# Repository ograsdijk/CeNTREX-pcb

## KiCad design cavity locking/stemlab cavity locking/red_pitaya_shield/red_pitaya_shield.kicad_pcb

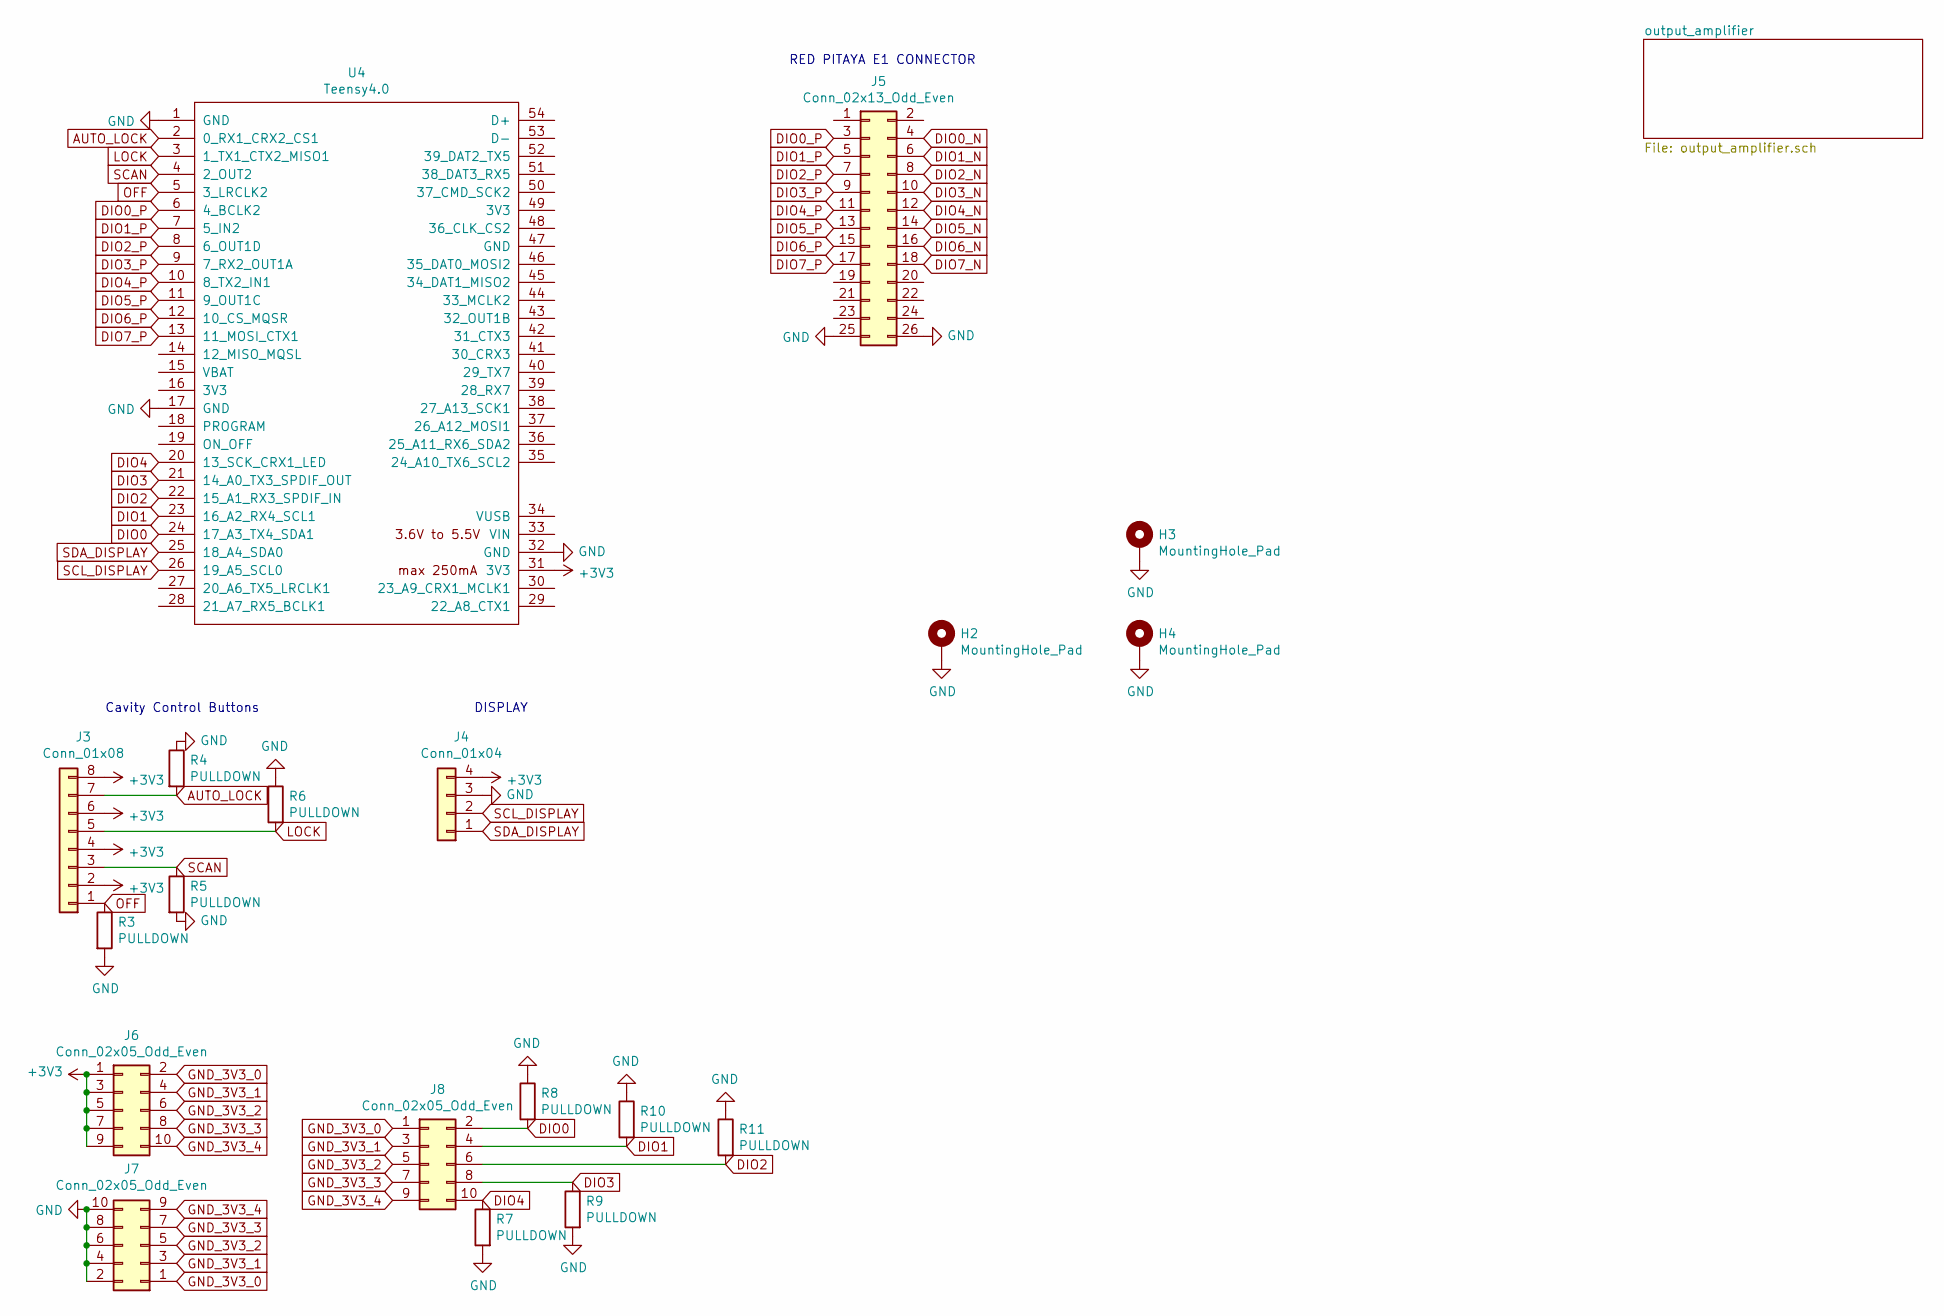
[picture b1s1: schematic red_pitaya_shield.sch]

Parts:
H2, H3, H4: MountingHole_Pad; MountingHole_3.2mm_M3_DIN965_Pad
J3: Conn_01x08; PinHeader_2x04_P2.54mm_Vertical
J4: Conn_01x04; PinHeader_1x04_P2.54mm_Vertical
J5: Conn_02x13_Odd_Even; IDC-Header_2x13_P2.54mm_Vertical
J6, J7, J8: Conn_02x05_Odd_Even; PinSocket_2x05_P2.54mm_Vertical
R3, R4, R5, R6, R7, R8, R9, R10, R11: PULLDOWN; R_0805_2012Metric
U4: Teensy4.0; Teensy40

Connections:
+3V3: J3.2, J3.4, J3.6, J3.8, J4.4, J6.1, J6.3, J6.5, J6.7, J6.9, U4.31 (3V3)
AUTO_LOCK: J3.7, R4.2, U4.2 (0_RX1_CRX2_CS1)
DIO0: J8.2, R8.2, U4.24 (17_A3_TX4_SDA1)
DIO0_N: J5.4
DIO0_P: J5.3, U4.6 (4_BCLK2)
DIO1: J8.4, R10.2, U4.23 (16_A2_RX4_SCL1)
DIO1_N: J5.6
DIO1_P: J5.5, U4.7 (5_IN2)
DIO2: J8.6, R11.2, U4.22 (15_A1_RX3_SPDIF_IN)
DIO2_N: J5.8
DIO2_P: J5.7, U4.8 (6_OUT1D)
DIO3: J8.8, R9.1, U4.21 (14_A0_TX3_SPDIF_OUT)
DIO3_N: J5.10
DIO3_P: J5.9, U4.9 (7_RX2_OUT1A)
DIO4: J8.10, R7.1, U4.20 (13_SCK_CRX1_LED)
DIO4_N: J5.12
DIO4_P: J5.11, U4.10 (8_TX2_IN1)
DIO5_N: J5.14
DIO5_P: J5.13, U4.11 (9_OUT1C)
DIO6_N: J5.16
DIO6_P: J5.15, U4.12 (10_CS_MQSR)
DIO7_N: J5.18
DIO7_P: J5.17, U4.13 (11_MOSI_CTX1)
GND: H2.1, H3.1, H4.1, J4.3, J5.25, J5.26, J7.2, J7.4, J7.6, J7.8, J7.10, R3.2, R4.1, R5.2, R6.1, R7.2, R8.1, R9.2, R10.1, R11.1, U4.1 (GND), U4.17 (GND), U4.32 (GND); also elsewhere on the board
GND_3V3_0: J6.2, J7.1, J8.1
GND_3V3_1: J6.4, J7.3, J8.3
GND_3V3_2: J6.6, J7.5, J8.5
GND_3V3_3: J6.8, J7.7, J8.7
GND_3V3_4: J6.10, J7.9, J8.9
LOCK: J3.5, R6.2, U4.3 (1_TX1_CTX2_MISO1)
OFF: J3.1, R3.1, U4.5 (3_LRCLK2)
SCAN: J3.3, R5.1, U4.4 (2_OUT2)
SCL_DISPLAY: J4.2, U4.26 (19_A5_SCL0)
SDA_DISPLAY: J4.1, U4.25 (18_A4_SDA0)

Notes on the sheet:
Cavity Control Buttons
RED PITAYA E1 CONNECTOR
DISPLAY

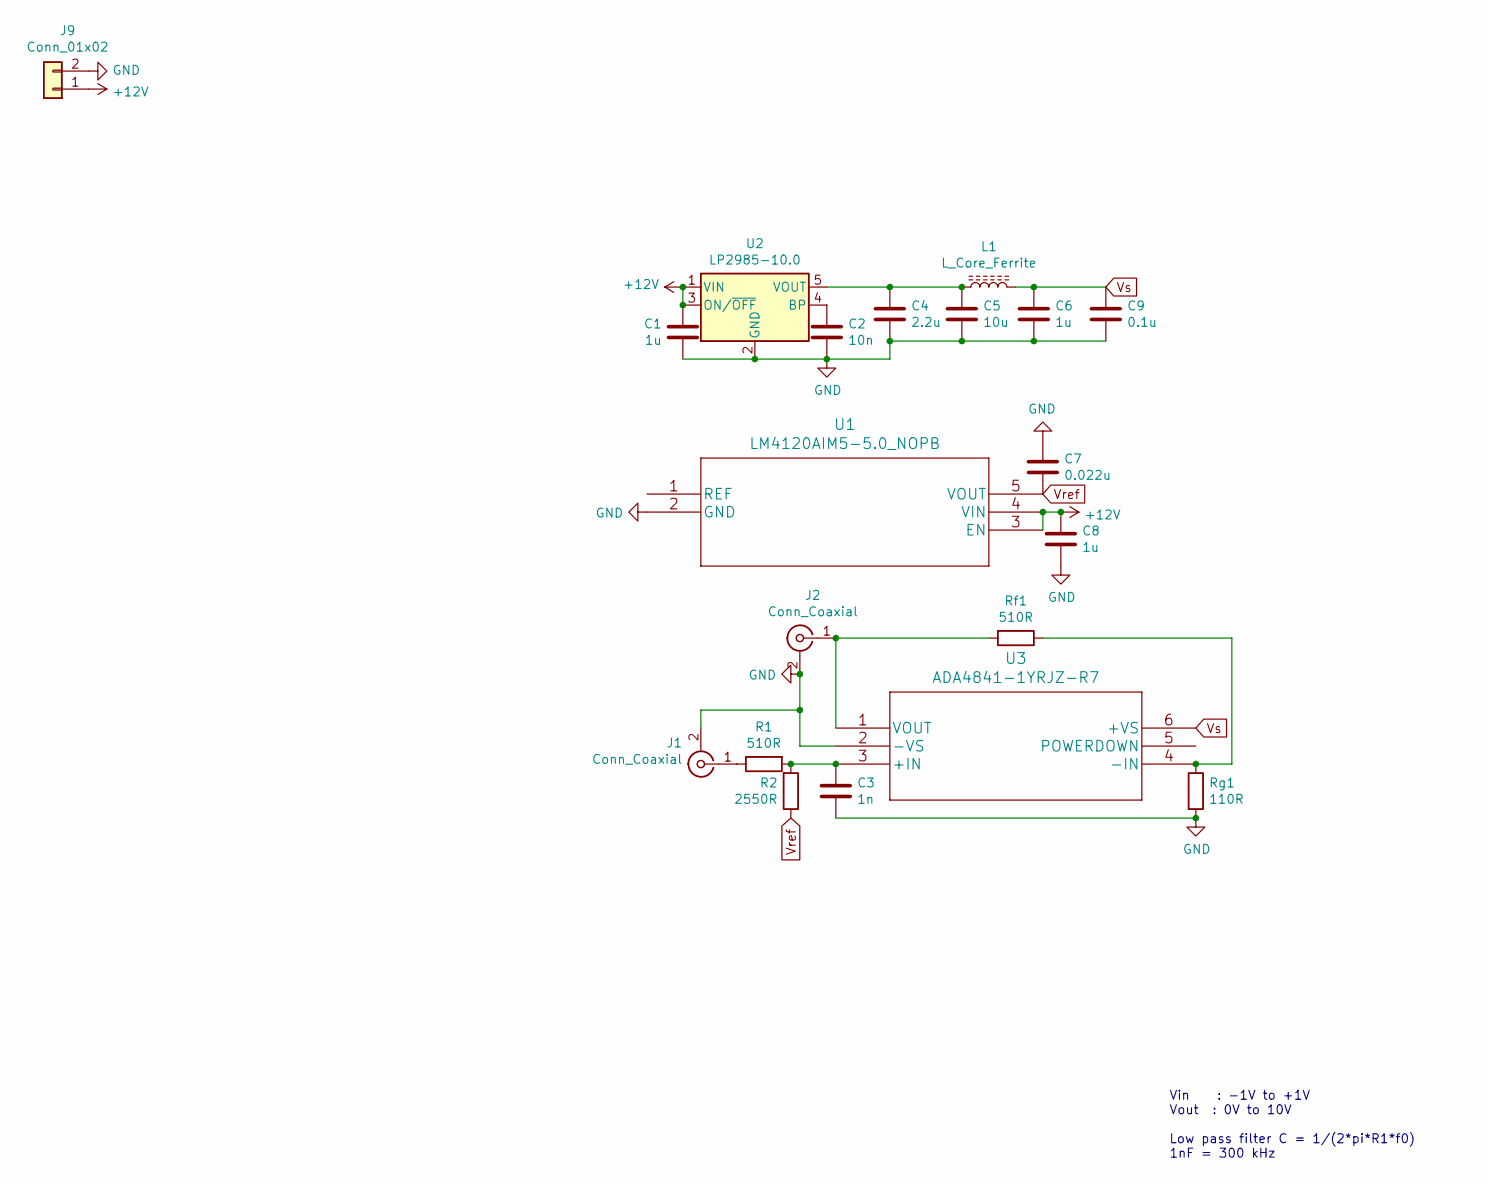
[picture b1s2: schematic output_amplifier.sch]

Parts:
C1, C6, C8: 1u; C_0805_2012Metric
C2: 10n; C_0805_2012Metric
C3: 1n; C_0805_2012Metric
C4: 2.2u; C_0805_2012Metric
C5: 10u; C_0805_2012Metric
C7: 0.022u; C_0805_2012Metric
C9: 0.1u; C_0805_2012Metric
J1, J2: Conn_Coaxial; SMA_Amphenol_132289_EdgeMount
J9: Conn_01x02; PinHeader_1x02_P2.54mm_Vertical
L1: L_Core_Ferrite; L_1206_3216Metric
R1: 510R; R_0805_2012Metric
R2: 2550R; R_0805_2012Metric
Rf1: 510R; R_0805_2012Metric
Rg1: 110R; R_0805_2012Metric
U1: LM4120AIM5-5.0_NOPB; LM4120AIM5-5.0&slash_NOPB
U2: LP2985-10.0; LP2985-10DBVR
U3: ADA4841-1YRJZ-R7

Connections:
+12V: C1.2, C8.1, J9.1, U1.3 (EN), U1.4 (VIN), U2.1 (VIN), U2.3 (ON/~OFF~)
GND: C1.1, C2.2, C3.2, C4.2, C5.2, C6.2, C7.2, C8.2, C9.2, J1.2 (Ext), J2.2 (Ext), J9.2, Rg1.2, U1.2 (GND), U2.2 (GND), U3.2 (-VS); also elsewhere on the board
unnamed: C2.1, U2.4 (BP)
unnamed: C3.1, R1.2, R2.2, U3.3 (+IN)
unnamed: C4.1, C5.1, L1.1, U2.5 (VOUT)
unnamed: J1.1 (In), R1.1
unnamed: J2.1 (In), Rf1.2, U3.1 (VOUT)
unnamed: Rf1.1, Rg1.1, U3.4 (-IN)
Vref: C7.1, R2.1, U1.5 (VOUT)
Vs: C6.1, C9.1, L1.2, U3.6 (+VS)

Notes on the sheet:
Vin : -1V to +1V Vout : 0V to 10V Low pass filter C = 1/(2*pi*R1*f0) 1nF = 300 kHz

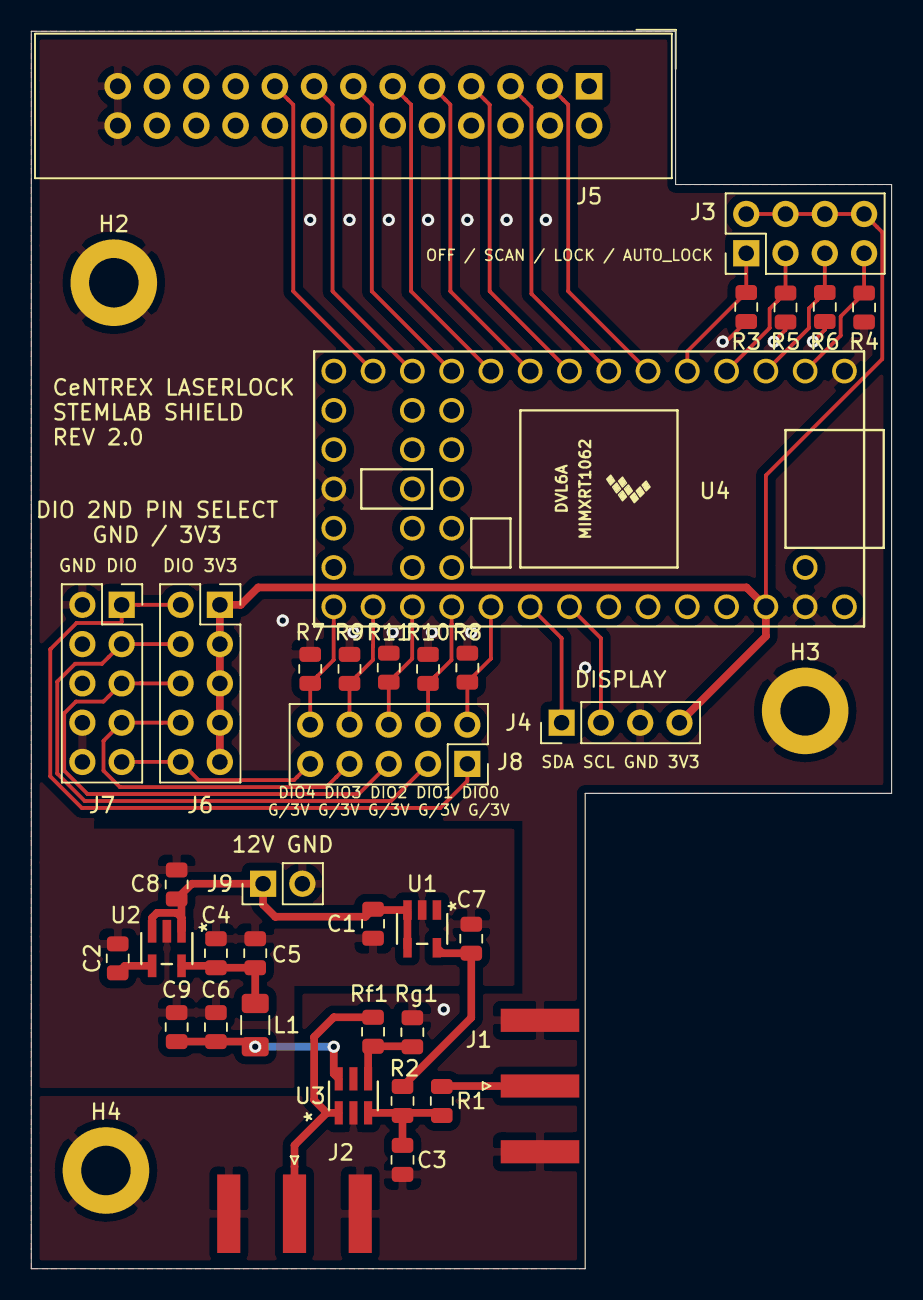
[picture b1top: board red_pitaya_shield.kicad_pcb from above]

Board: 2 copper layers, 55.6 x 80.0 mm, 39 parts (0 on the bottom side), 35 nets.

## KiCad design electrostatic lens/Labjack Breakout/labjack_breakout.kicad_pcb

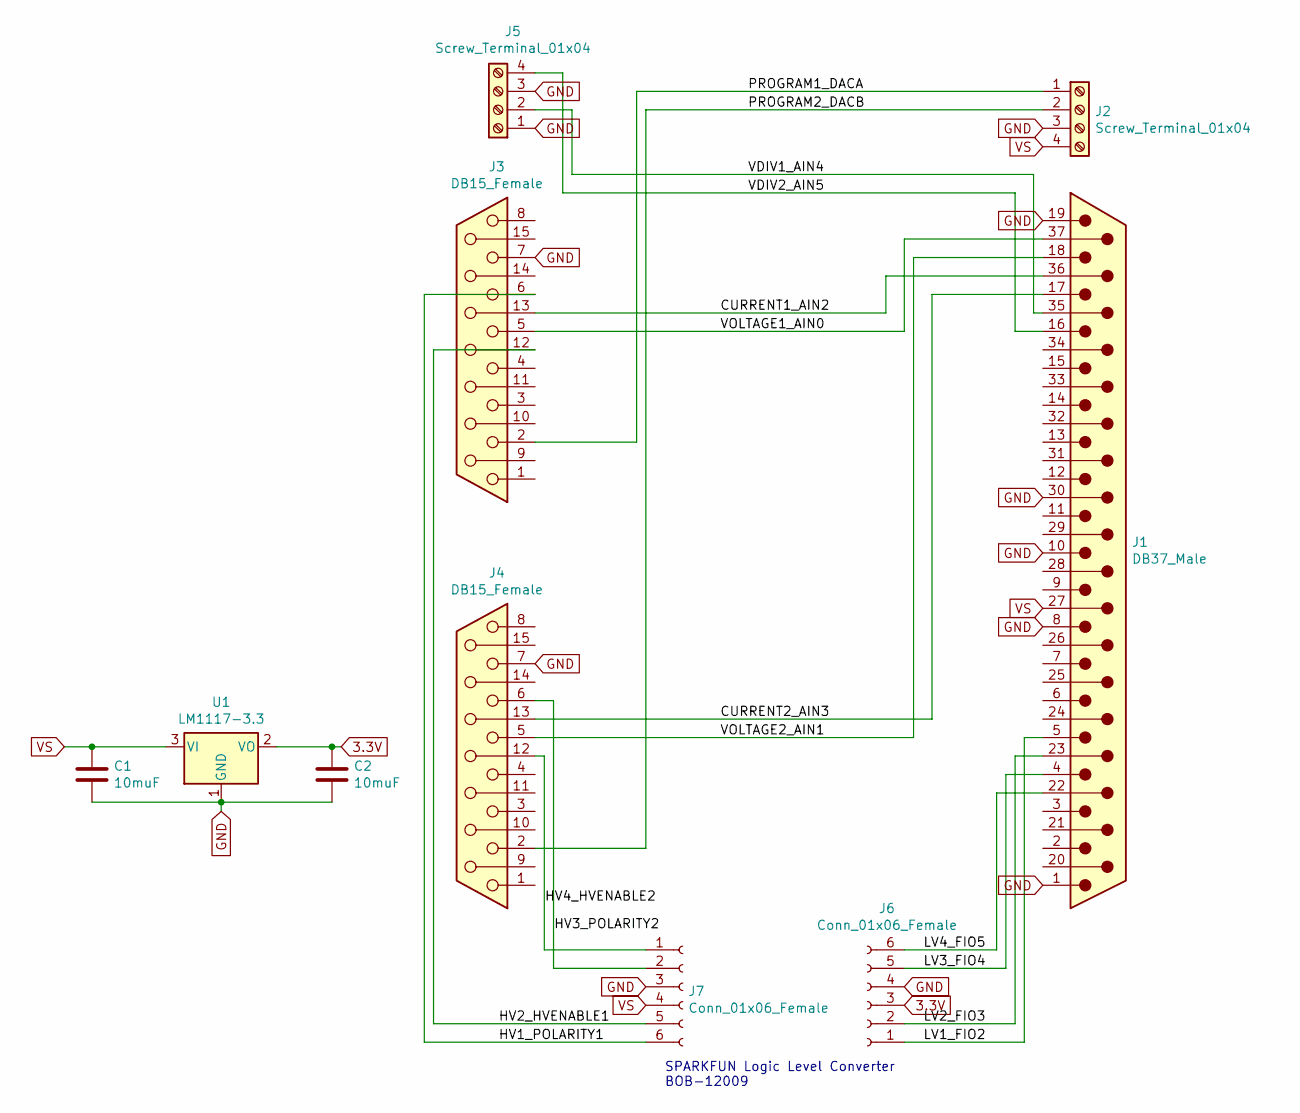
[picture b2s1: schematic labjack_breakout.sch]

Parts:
C1, C2: 10muF; CP_Axial_L10.0mm_D4.5mm_P15.00mm_Horizontal
J1: DB37_Male; DSUB-37_Male_Horizontal_P2.77x2.84mm_EdgePinOffset7.70mm_Ho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
J2, J5: Screw_Terminal_01x04; TerminalBlock_RND_205-00003_1x04_P5.00mm_Horizontal
J3, J4: DB15_Female; DSUB-15_Female_Horizontal_P2.77x2.84mm_EdgePinOffset7.70mm_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
J6, J7: Conn_01x06_Female; PinSocket_1x06_P2.54mm_Vertical
U1: LM1117-3.3; TO-220-3_Vertical

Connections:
3.3V: C2.1, J6.3, U1.2 (VO)
/CURRENT1_AIN2: J1.36, J3.13
/CURRENT2_AIN3: J1.17, J4.13
/HV1_POLARITY1: J3.6, J7.6
/HV2_HVENABLE1: J3.12, J7.5
/HV3_POLARITY2: J4.6, J7.2
/HV4_HVENABLE2: J4.12, J7.1
/LV1_FIO2: J1.5, J6.1
/LV2_FIO3: J1.23, J6.2
/LV3_FIO4: J1.4, J6.5
/LV4_FIO5: J1.22, J6.6
/PROGRAM1_DACA: J2.1, J3.2
/PROGRAM2_DACB: J2.2, J4.2
/VDIV1_AIN4: J1.35, J5.2
/VDIV2_AIN5: J1.16, J5.4
/VOLTAGE1_AIN0: J1.37, J3.5
/VOLTAGE2_AIN1: J1.18, J4.5
GND: C1.2, C2.2, J1.1, J1.8, J1.10, J1.19, J1.30, J2.3, J3.7, J4.7, J5.1, J5.3, J6.4, J7.3, U1.1 (GND)
VS: C1.1, J1.27, J2.4, J7.4, U1.3 (VI)

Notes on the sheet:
SPARKFUN Logic Level Converter BOB-12009

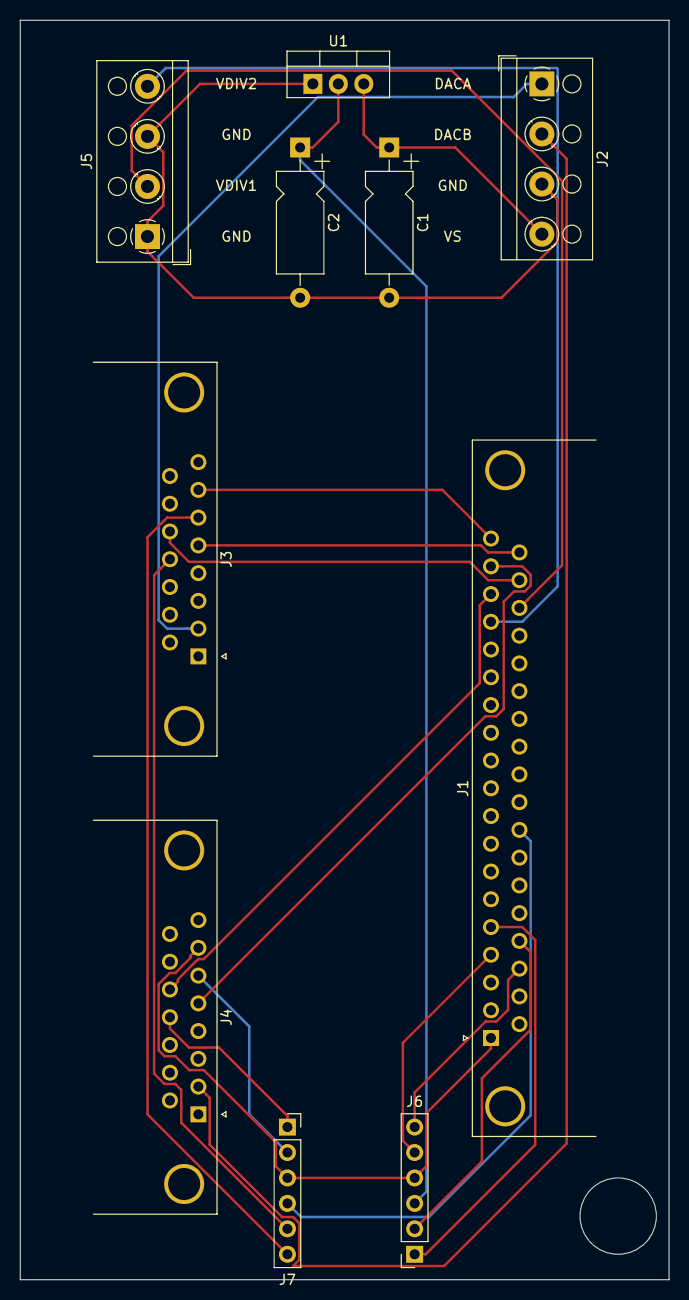
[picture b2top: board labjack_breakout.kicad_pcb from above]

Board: 2 copper layers, 64.8 x 125.7 mm, 10 parts (0 on the bottom side), 19 nets.

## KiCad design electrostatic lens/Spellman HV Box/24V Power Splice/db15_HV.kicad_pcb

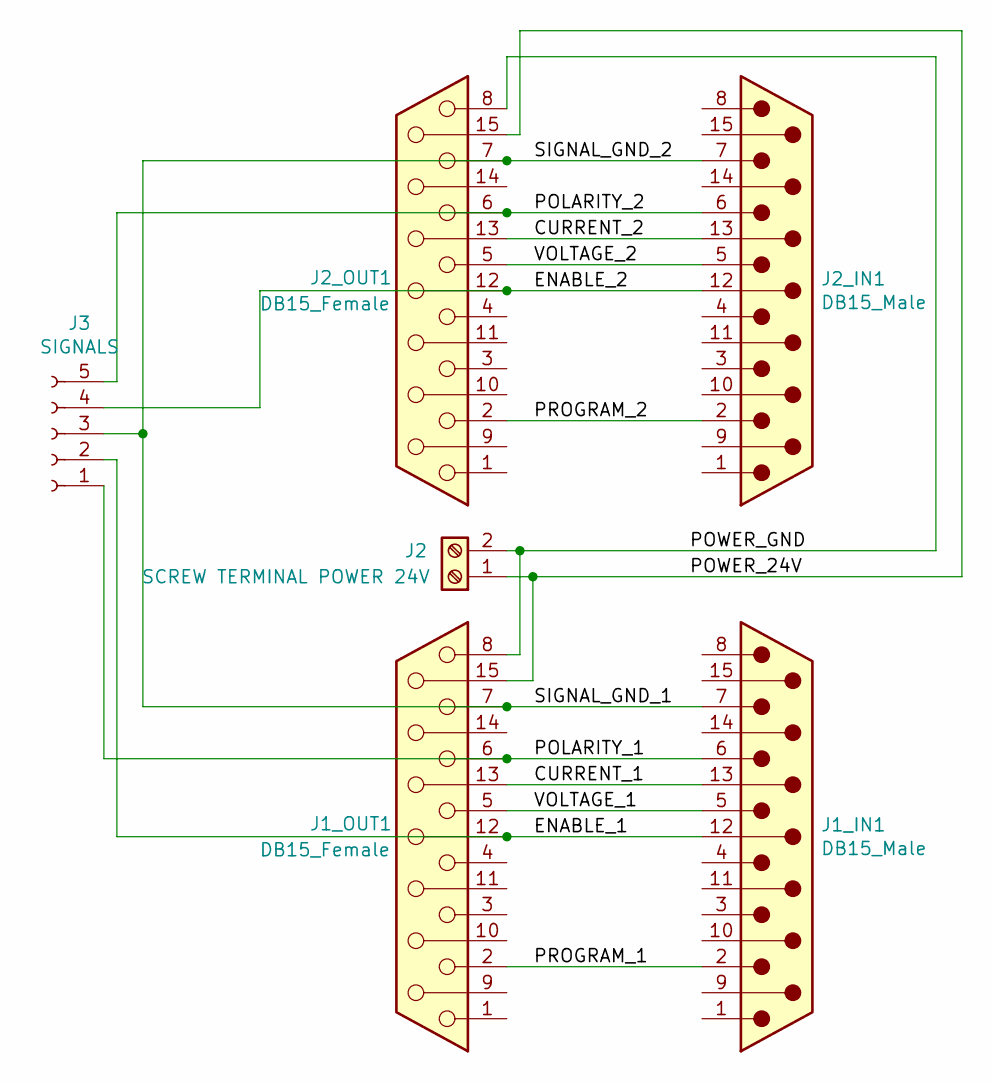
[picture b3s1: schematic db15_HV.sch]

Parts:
J1_IN1, J2_IN1: DB15_Male; DSUB-15_Male_Horizontal_P2.77x2.84mm_EdgePinOffset4.94mm_Ho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
J1_OUT1, J2_OUT1: DB15_Female; DSUB-15_Female_Horizontal_P2.77x2.84mm_EdgePinOffset4.94mm_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
J2: SCREW TERMINAL POWER 24V; TerminalBlock_RND_205-00001_1x02_P5.00mm_Horizontal
J3: SIGNALS; PinSocket_1x05_P2.54mm_Vertical

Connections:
/CURRENT_1: J1_IN1.13, J1_OUT1.13
/CURRENT_2: J2_IN1.13, J2_OUT1.13
/ENABLE_1: J1_IN1.12, J1_OUT1.12, J3.2
/ENABLE_2: J2_IN1.12, J2_OUT1.12, J3.4
/POLARITY_1: J1_IN1.6, J1_OUT1.6, J3.1
/POLARITY_2: J2_IN1.6, J2_OUT1.6, J3.5
/POWER_24V: J1_OUT1.15, J2.1, J2_OUT1.15
/POWER_GND: J1_OUT1.8, J2.2, J2_OUT1.8
/PROGRAM_1: J1_IN1.2, J1_OUT1.2
/PROGRAM_2: J2_IN1.2, J2_OUT1.2
/SIGNAL_GND_1: J1_IN1.7, J1_OUT1.7, J2_IN1.7, J2_OUT1.7, J3.3
/VOLTAGE_1: J1_IN1.5, J1_OUT1.5
/VOLTAGE_2: J2_IN1.5, J2_OUT1.5

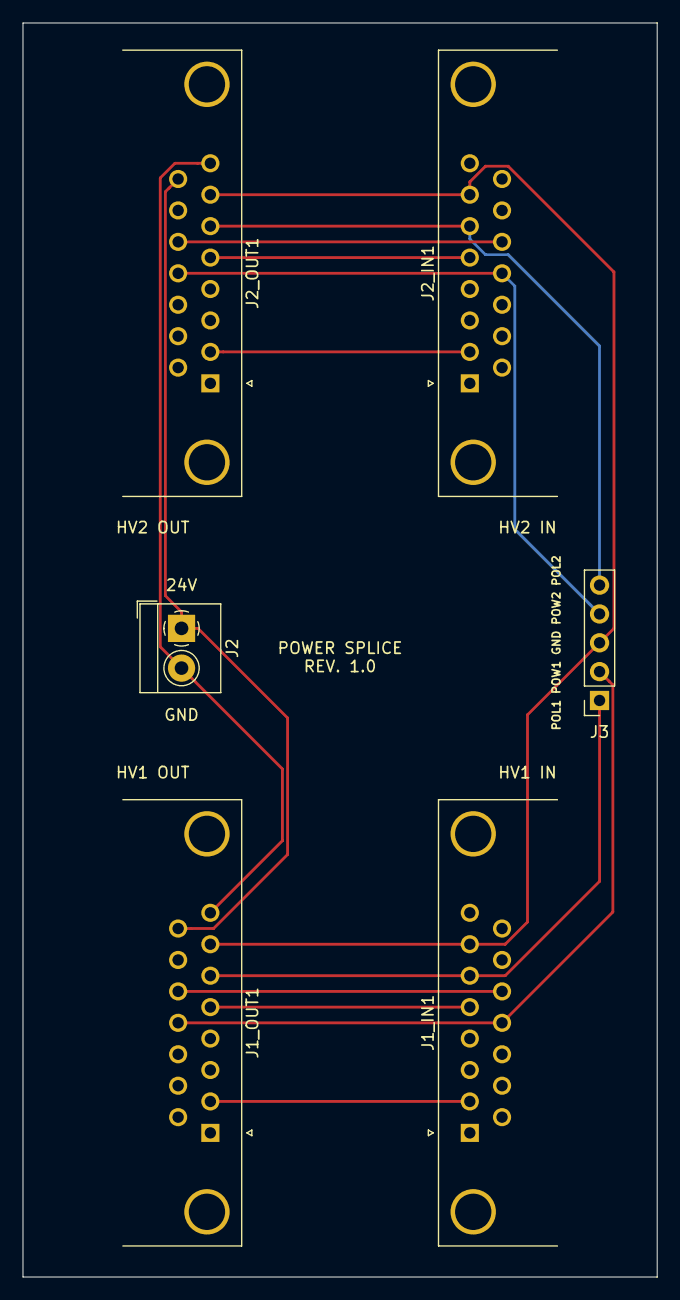
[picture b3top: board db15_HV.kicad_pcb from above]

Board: 2 copper layers, 55.9 x 110.5 mm, 6 parts (0 on the bottom side), 13 nets.

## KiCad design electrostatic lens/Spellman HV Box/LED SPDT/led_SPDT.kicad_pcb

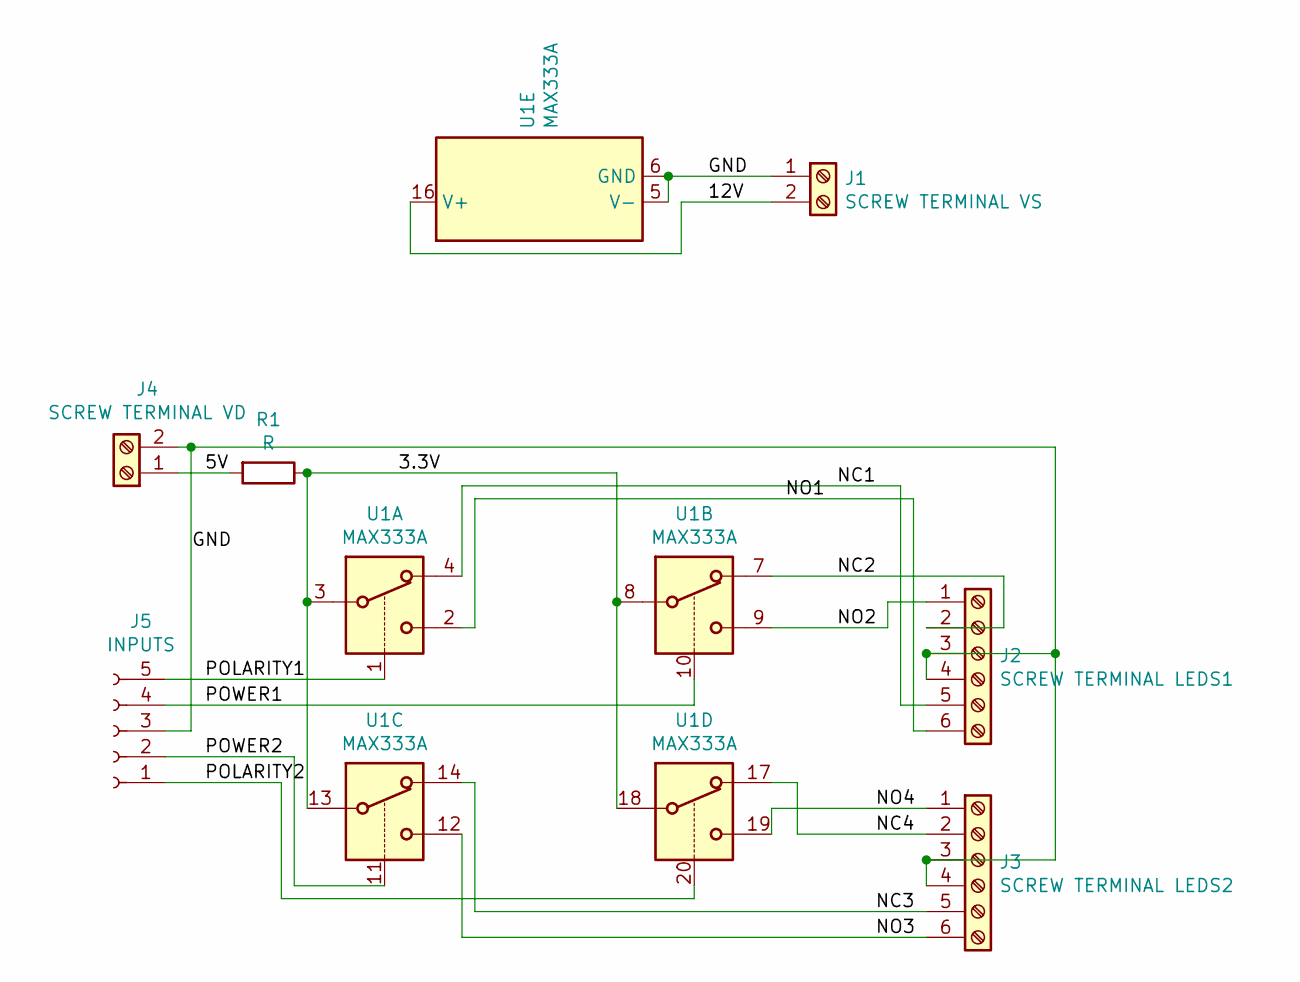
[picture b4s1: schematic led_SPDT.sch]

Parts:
J1: SCREW TERMINAL VS; TerminalBlock_RND_205-00001_1x02_P5.00mm_Horizontal
J2: SCREW TERMINAL LEDS1; TerminalBlock_RND_205-00005_1x06_P5.00mm_Horizontal
J3: SCREW TERMINAL LEDS2; TerminalBlock_RND_205-00005_1x06_P5.00mm_Horizontal
J4: SCREW TERMINAL VD; TerminalBlock_RND_205-00001_1x02_P5.00mm_Horizontal
J5: INPUTS; PinSocket_1x05_P2.54mm_Vertical
R1: R; R_Axial_DIN0207_L6.3mm_D2.5mm_P7.62mm_Horizontal
U1: MAX333A; DIP-20_W7.62mm_Socket

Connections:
/3.3V: R1.1, U1.3, U1.8, U1.13, U1.18
/5V: J4.1, R1.2
/12V: J1.2, U1.16 (V+)
/GND: J1.1, J2.3, J2.4, J3.3, J3.4, J4.2, J5.3, U1.5 (V-), U1.6 (GND)
/NC1: J2.5, U1.4
/NC2: J2.2, U1.7
/NC3: J3.5, U1.14
/NC4: J3.2, U1.17
/NO1: J2.6, U1.2
/NO2: J2.1, U1.9
/NO3: J3.6, U1.12
/NO4: J3.1, U1.19
/POLARITY1: J5.5, U1.1
/POLARITY2: J5.1, U1.20
/POWER1: J5.4, U1.10
/POWER2: J5.2, U1.11

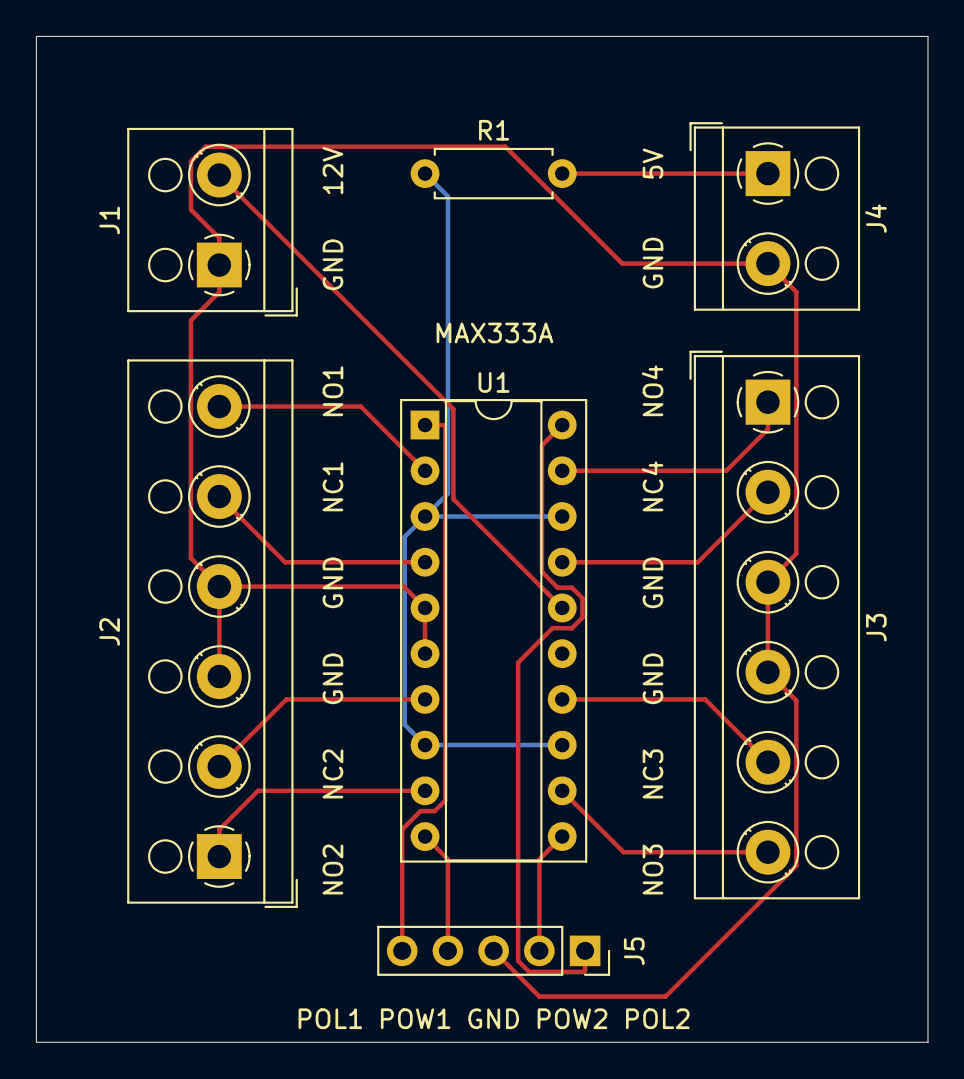
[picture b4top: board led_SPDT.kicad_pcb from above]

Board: 2 copper layers, 49.5 x 55.9 mm, 7 parts (0 on the bottom side), 16 nets.

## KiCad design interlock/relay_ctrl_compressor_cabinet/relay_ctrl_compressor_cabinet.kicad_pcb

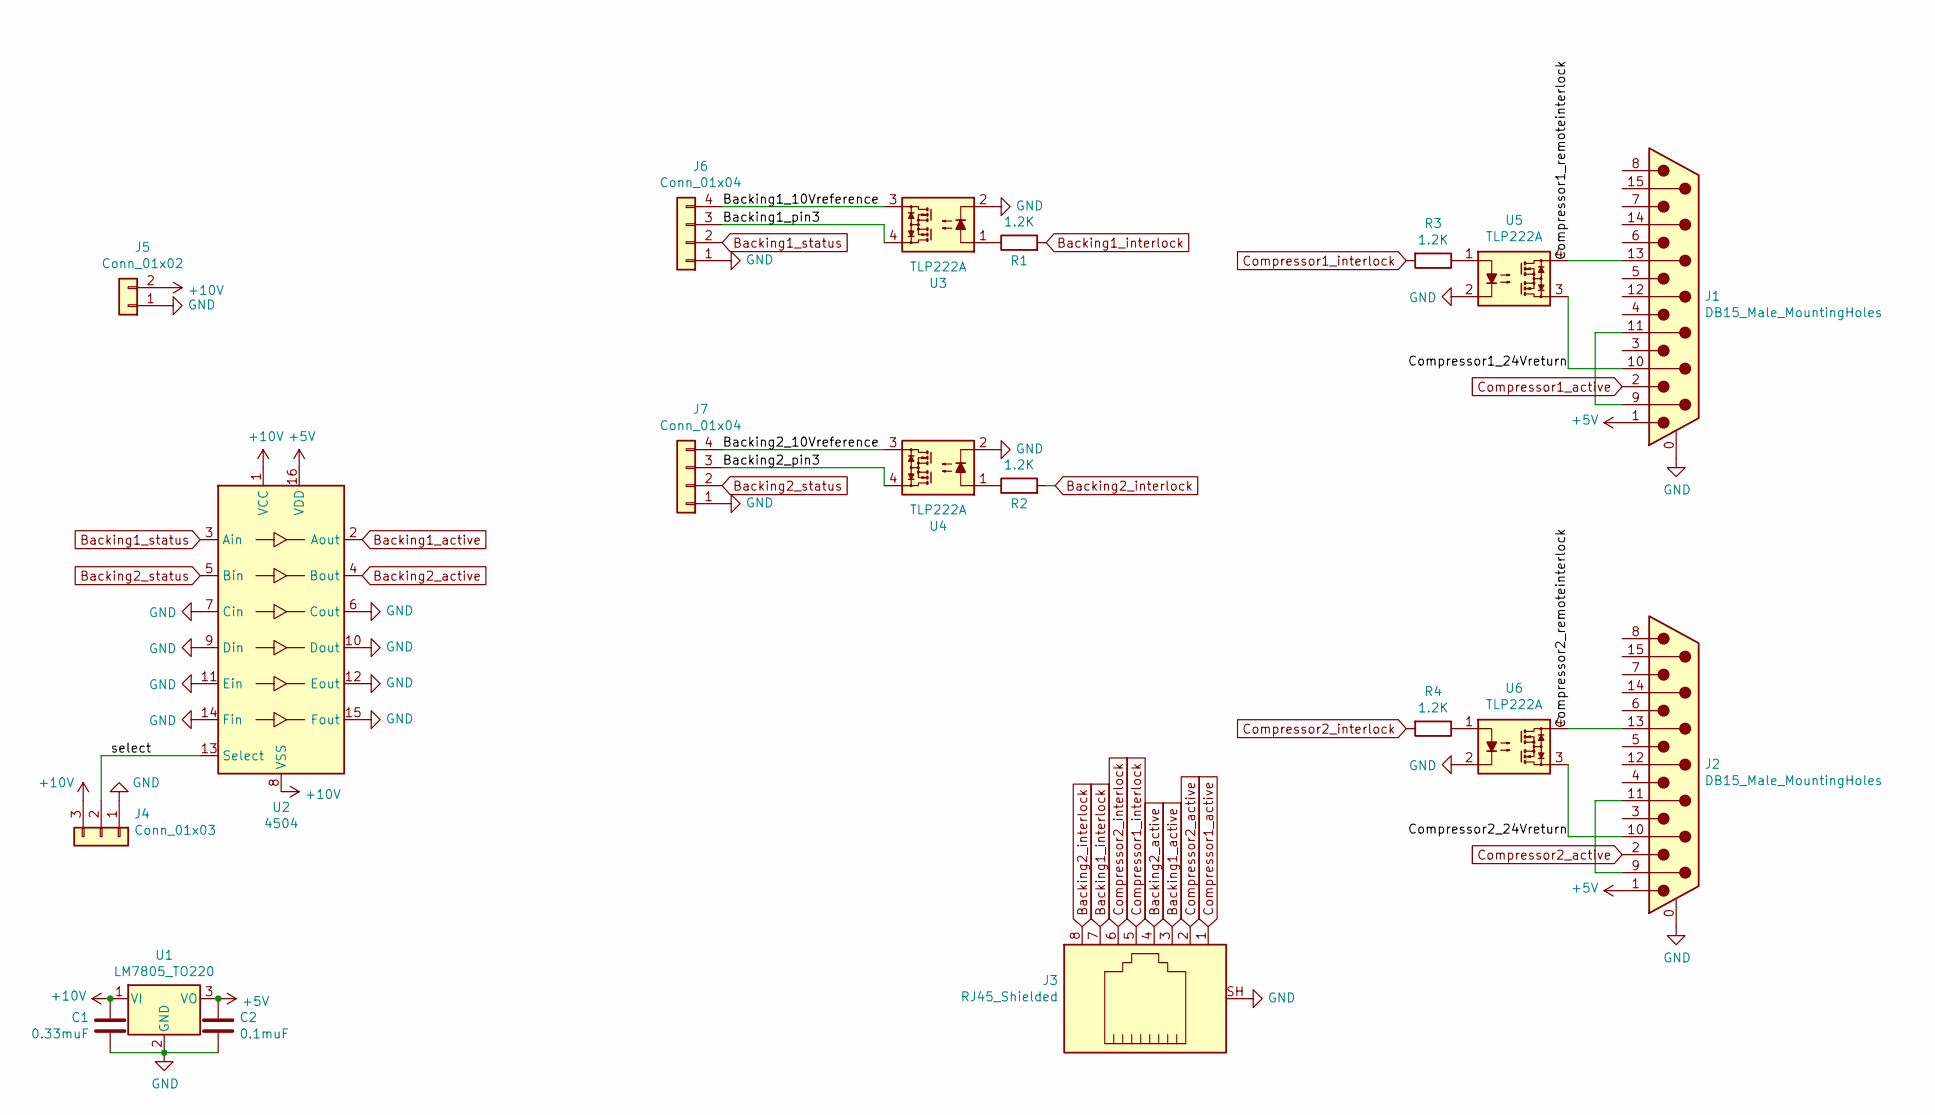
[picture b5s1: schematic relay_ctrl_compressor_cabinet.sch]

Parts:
C1: 0.33muF; CP_Radial_D4.0mm_P1.50mm
C2: 0.1muF; CP_Radial_D5.0mm_P2.50mm
J1, J2: DB15_Male_MountingHoles; DSUB-15_Male_Horizontal_P2.77x2.84mm_EdgePinOffset7.70mm_Ho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
J3: RJ45_Shielded; RJ45_Amphenol_RJHSE5380
J4: Conn_01x03; PinHeader_1x03_P2.54mm_Vertical
J5: Conn_01x02; PinHeader_1x02_P2.54mm_Vertical
J6, J7: Conn_01x04; PinHeader_1x04_P2.54mm_Vertical
R1, R2, R3, R4: 1.2K; R_Axial_DIN0207_L6.3mm_D2.5mm_P7.62mm_Horizontal
U1: LM7805_TO220; TO-220-3_Vertical
U2: 4504; DIP-16_W7.62mm_Socket
U3, U4, U5, U6: TLP222A; DIP-4_W7.62mm

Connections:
+5V: C2.1, J1.1, J2.1, U1.3 (VO), U2.16 (VDD)
/Backing1_10Vreference: J6.4, U3.3
/Backing1_pin3: J6.3, U3.4
/Backing2_10Vreference: J7.4, U4.3
/Backing2_pin3: J7.3, U4.4
/Compressor1_24Vreturn: J1.10, U5.3
/Compressor1_remoteinterlock: J1.13, U5.4
/Compressor2_24Vreturn: J2.10, U6.3
/Compressor2_remoteinterlock: J2.13, U6.4
/select: J4.2, U2.13 (Select)
Backing1_active: J3.3, U2.2 (Aout)
Backing1_interlock: J3.7, R1.2
Backing1_status: J6.2, U2.3 (Ain)
Backing2_active: J3.4, U2.4 (Bout)
Backing2_interlock: J3.8, R2.2
Backing2_status: J7.2, U2.5 (Bin)
Compressor1_active: J1.2, J3.1
Compressor1_interlock: J3.5, R3.2
Compressor2_active: J2.2, J3.2
Compressor2_interlock: J3.6, R4.2
unnamed: J1.9, J1.11 (P111)
unnamed: J2.9, J2.11 (P111)
unnamed: R1.1, U3.1
unnamed: R2.1, U4.1
unnamed: R3.1, U5.1
unnamed: R4.1, U6.1

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
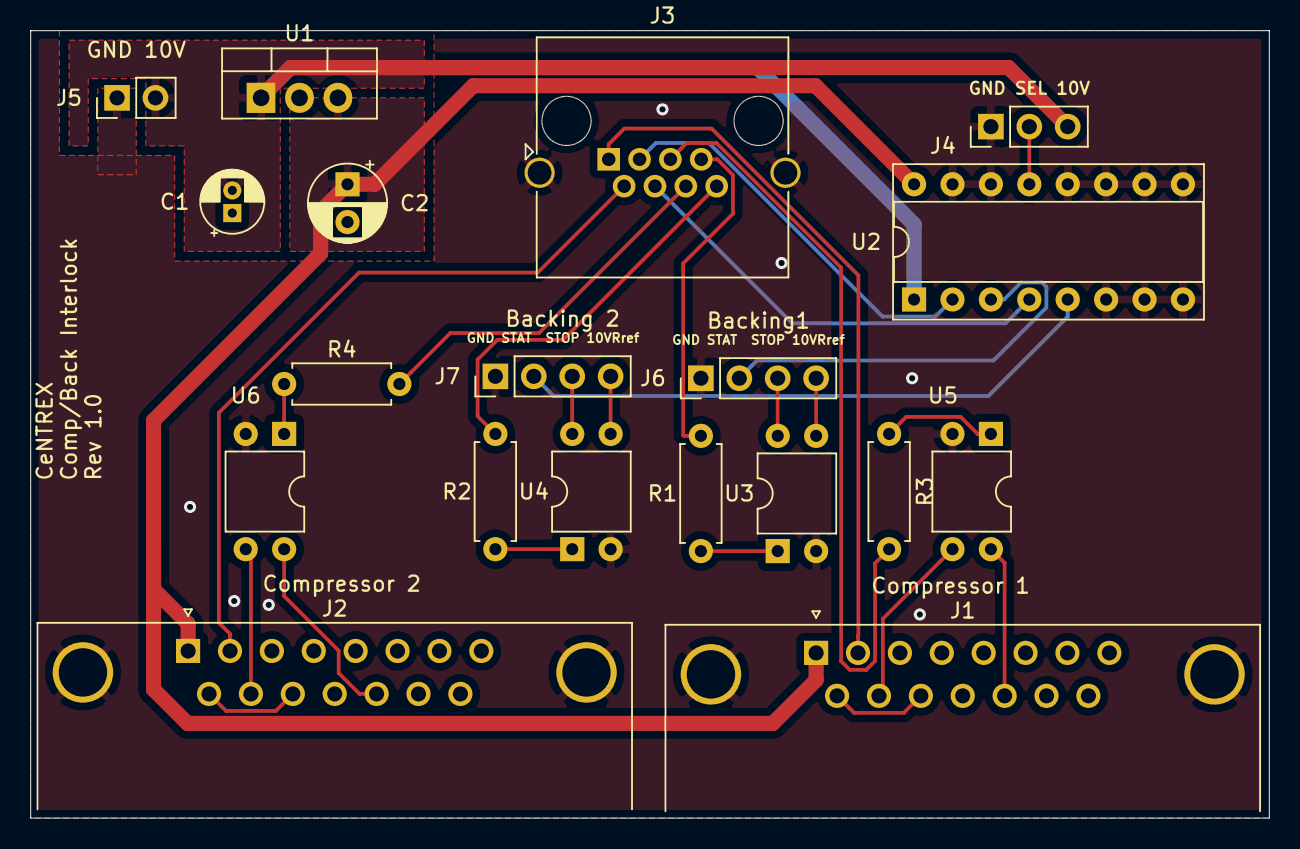
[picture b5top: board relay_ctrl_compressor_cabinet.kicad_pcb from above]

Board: 2 copper layers, 81.9 x 52.1 mm, 19 parts (0 on the bottom side), 28 nets.

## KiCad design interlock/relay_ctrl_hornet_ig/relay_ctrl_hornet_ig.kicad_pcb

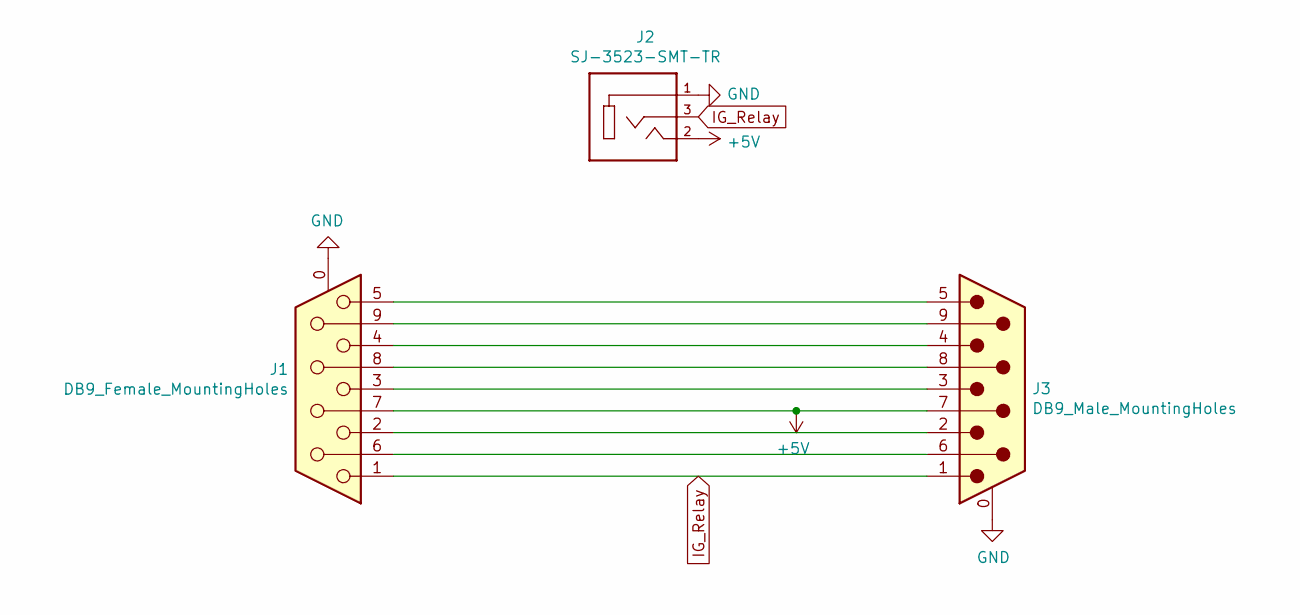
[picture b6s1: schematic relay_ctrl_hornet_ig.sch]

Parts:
J1: DB9_Female_MountingHoles; DSUB-9_Female_Horizontal_P2.77x2.84mm_EdgePinOffset4.94mm_H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
J2: SJ-3523-SMT-TR; CUI_SJ-3523-SMT-TR
J3: DB9_Male_MountingHoles; DSUB-9_Male_Horizontal_P2.77x2.84mm_EdgePinOffset4.94mm_Hou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

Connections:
+5V: J1.7, J2.2, J3.7
GND: J1.0 (PAD), J2.1, J3.0 (PAD)
IG_Relay: J1.1, J2.3, J3.1
unnamed: J1.2, J3.2
unnamed: J1.3, J3.3
unnamed: J1.4, J3.4
unnamed: J1.5, J3.5
unnamed: J1.6, J3.6
unnamed: J1.8, J3.8
unnamed: J1.9, J3.9

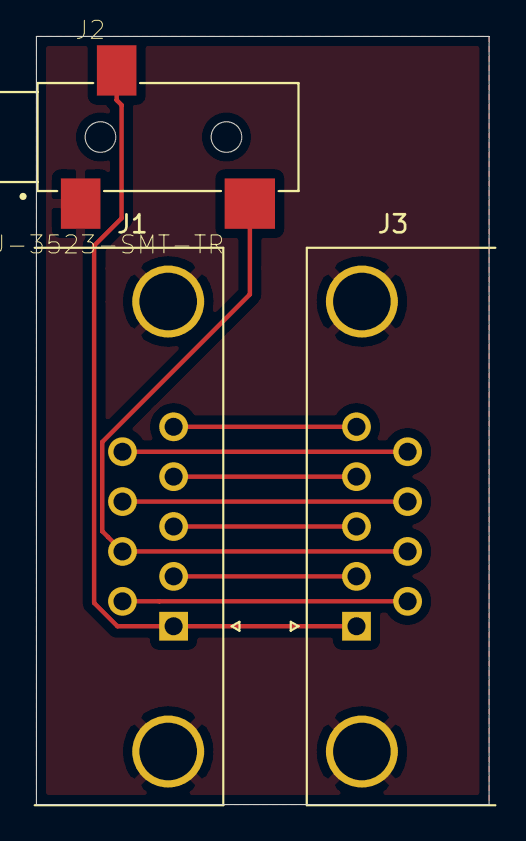
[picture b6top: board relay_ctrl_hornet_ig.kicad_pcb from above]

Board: 2 copper layers, 25.1 x 42.7 mm, 3 parts (0 on the bottom side), 10 nets.
